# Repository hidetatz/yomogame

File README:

== Emulators & licensing

NES — src/nes/ is copied and modified from Esp32-S3-nes-emulator-by-DSN (https://github.com/derdacavga/Esp32-S3-nes-emulator-by-DSN) imported at commit 030c4b8.
Some modifications are made.

Game Boy — src/gb/ is copied and modified from Peanut-GB (https://github.com/deltabeard/Peanut-GB) .
Some modifications are made.

== License

The upstream NES emulator code is licensed under the GNU General Public
License v3 (see the LICENSE file, copied from the DSN repository; the
Nofrendo core originates as GPL‑licensed code by Matthew Conte). src/nes/ in
this repository is a derivative work and remains under the GPL.

Peanut-GB and minigb_apu (src/gb/) are under the MIT License (see
src/gb/peanut_gb.h and src/gb/LICENSE.minigb_apu); their notices are retained.
MIT imposes no copyleft, but this code is combined into the same binary as the
GPL NES core, so the paragraph below applies to the whole firmware regardless.

Because the yomogame firmware links this GPL code into a single program,
any distribution of a built yomogame binary (or of a device running it) is
subject to the GPL: recipients must be able to obtain the complete
corresponding source code under the same terms. For that reason this repository
as a whole is distributed under GPL‑3.0‑or‑later.

The first‑party parts of this project (lib/audio, lib/input,
lib/volume_overlay, src/tetris/, src/scene.h, src/frame_pusher.h,
src/yomogame.h, src/main.cpp, src/gb/gb_scene.h, src/gb/gb_core.c) are
written by the yomogame author. They are released here under the GPL as part of
the combined work.

== Assets

Background music and sound effects are used courtesy of:

イワシロ音楽素材
https://iwashiro-sounds.work/

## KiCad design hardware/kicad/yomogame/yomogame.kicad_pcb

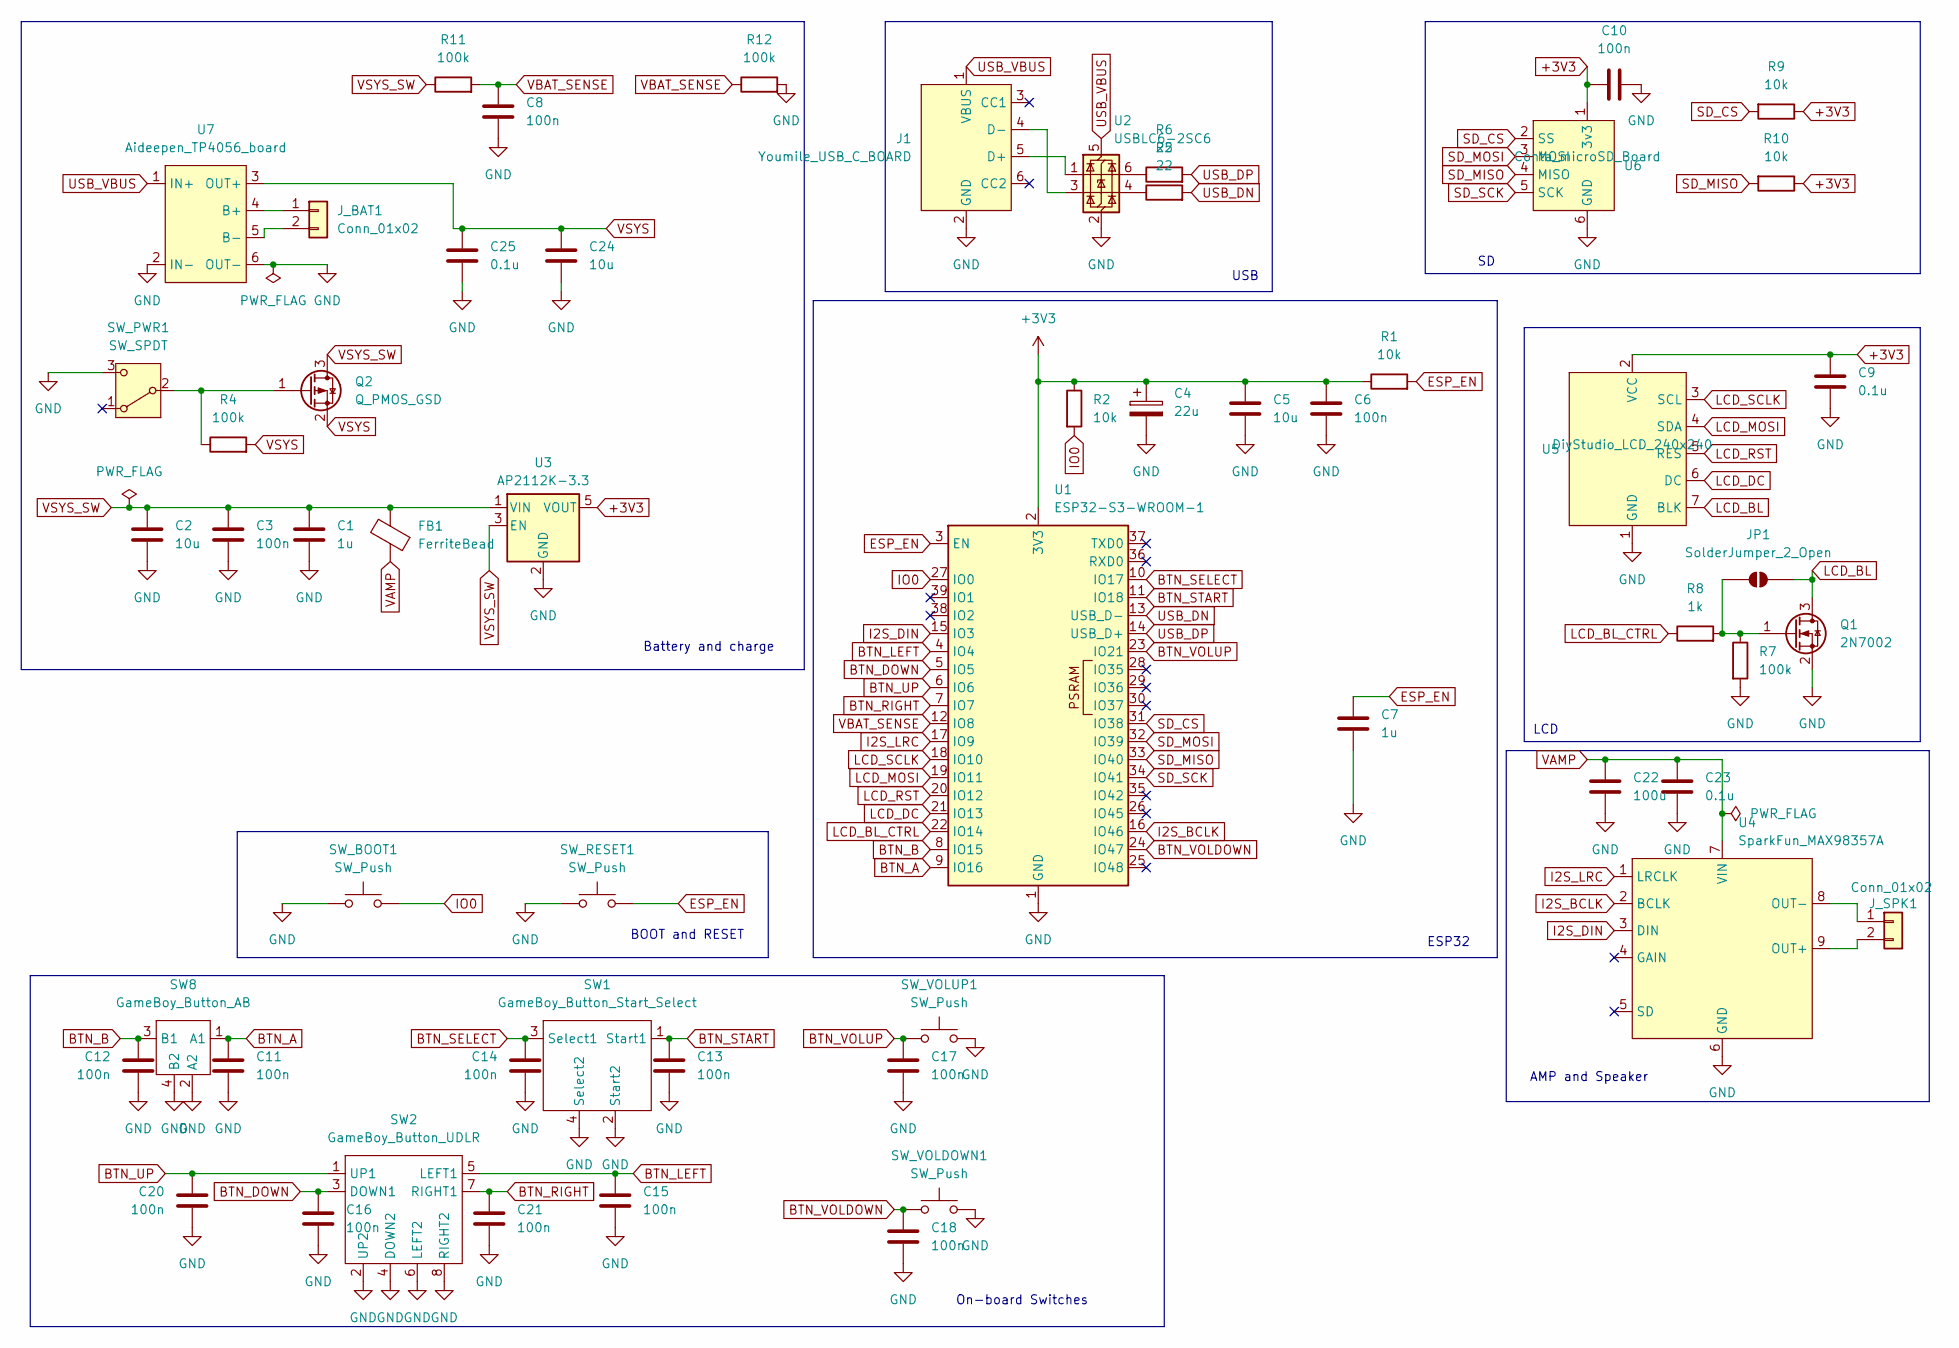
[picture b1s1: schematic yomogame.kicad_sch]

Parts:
C1, C7: 1u; C_0805_2012Metric_Pad1.18x1.45mm_HandSolder
C2, C5, C24: 10u; C_0805_2012Metric_Pad1.18x1.45mm_HandSolder
C3, C6, C8, C10, C11, C12, C13, C14, C15, C16, C17, C18, C20, C21: 100n; C_0805_2012Metric_Pad1.18x1.45mm_HandSolder
C4: 22u; C_1206_3216Metric_Pad1.33x1.80mm_HandSolder
C9, C23, C25: 0.1u; C_0805_2012Metric_Pad1.18x1.45mm_HandSolder
C22: 100u; CP_Radial_D5.0mm_P2.50mm
FB1: FerriteBead; L_0805_2012Metric_Pad1.05x1.20mm_HandSolder
J1: Youmile_USB_C_BOARD
JP1: SolderJumper_2_Open; SolderJumper-2_P1.3mm_Open_Pad1.0x1.5mm
J_BAT1: Conn_01x02; JST_PH_B2B-PH-K_1x02_P2.00mm_Vertical
J_SPK1: Conn_01x02; JST_PH_B2B-PH-K_1x02_P2.00mm_Vertical
Q1: 2N7002; SOT-23_Handsoldering
Q2: Q_PMOS_GSD; SOT-23_Handsoldering
R1, R2, R9, R10: 10k; R_0805_2012Metric_Pad1.20x1.40mm_HandSolder
R4, R7, R11, R12: 100k; R_0805_2012Metric_Pad1.20x1.40mm_HandSolder
R5, R6: 22; R_0805_2012Metric_Pad1.20x1.40mm_HandSolder
R8: 1k; R_0805_2012Metric_Pad1.20x1.40mm_HandSolder
SW1: GameBoy_Button_Start_Select; BTN_start_select
SW2: GameBoy_Button_UDLR; BTN_UDLR
SW8: GameBoy_Button_AB; BTN_AB
SW_BOOT1: SW_Push; SW_PUSH_6mm
SW_PWR1: SW_SPDT; SW_Slide_SPDT_SK-12D11VG3
SW_RESET1: SW_Push; SW_PUSH_6mm
SW_VOLDOWN1: SW_Push; SW_SMD_Side_THAU13-AB-R
SW_VOLUP1: SW_Push; SW_SMD_Side_THAU13-AB-R
U1: ESP32-S3-WROOM-1
U2: USBLC6-2SC6; SOT-23-6_Handsoldering
U3: AP2112K-3.3; SOT-23-5_HandSoldering
U4: SparkFun_MAX98357A; AMP_SparkFun_MAX98357A_I2S_AUDIO
U5: DiyStudio_LCD_240x240
U6: Conta_microSD_Board
U7: Aideepen_TP4056_board

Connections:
+3V3: C4.1, C5.1, C6.1, C9.1, C10.1, R1.1, R2.1, R9.1, R10.1, U1.2 (3V3), U3.5 (VOUT), U5.2 (VCC), U6.1 (3v3)
BTN_A: C11.1, SW8.1 (A1), U1.9 (IO16)
BTN_B: C12.1, SW8.3 (B1), U1.8 (IO15)
BTN_DOWN: C16.1, SW2.3 (DOWN1), U1.5 (IO5)
BTN_LEFT: C15.1, SW2.5 (LEFT1), U1.4 (IO4)
BTN_RIGHT: C21.1, SW2.7 (RIGHT1), U1.7 (IO7)
BTN_SELECT: C14.1, SW1.3 (Select1), U1.10 (IO17)
BTN_START: C13.1, SW1.1 (Start1), U1.11 (IO18)
BTN_UP: C20.1, SW2.1 (UP1), U1.6 (IO6)
BTN_VOLDOWN: C18.1, SW_VOLDOWN1.1, U1.24 (IO47)
BTN_VOLUP: C17.1, SW_VOLUP1.1, U1.23 (IO21)
ESP_EN: C7.1, R1.2, SW_RESET1.2, U1.3 (EN)
GND: C1.2, C2.2, C3.2, C4.2, C5.2, C6.2, C7.2, C8.2, C9.2, C10.2, C11.2, C12.2, C13.2, C14.2, C15.2, C16.2, C17.2, C18.2, C20.2, C21.2, C22.2, C23.2, C24.2, C25.2, J1.2 (GND), Q1.2 (S), R7.2, R12.2, SW1.2 (Start2), SW1.4 (Select2), SW2.2 (UP2), SW2.4 (DOWN2), SW2.6 (LEFT2), SW2.8 (RIGHT2), SW8.2 (A2), SW8.4 (B2), SW_BOOT1.1, SW_PWR1.3 (C), SW_RESET1.1, SW_VOLDOWN1.2, SW_VOLUP1.2, U1.1 (GND), U1.40 (GND), U1.41 (GND), U2.2 (GND), U3.2 (GND), U4.6 (GND), U5.1 (GND), U6.6 (GND), U7.2 (IN-), U7.6 (OUT-)
I2S_BCLK: U1.16 (IO46), U4.2 (BCLK)
I2S_DIN: U1.15 (IO3), U4.3 (DIN)
I2S_LRC: U1.17 (IO9), U4.1 (LRCLK)
IO0: R2.2, SW_BOOT1.2, U1.27 (IO0)
LCD_BL: JP1.2 (B), Q1.3 (D), U5.7 (BLK)
LCD_BL_CTRL: R8.1, U1.22 (IO14)
LCD_DC: U1.21 (IO13), U5.6 (DC)
LCD_MOSI: U1.19 (IO11), U5.4 (SDA)
LCD_RST: U1.20 (IO12), U5.5 (RES)
LCD_SCLK: U1.18 (IO10), U5.3 (SCL)
unnamed: J1.5 (D+), U2.1 (I/O1)
unnamed: J1.4 (D-), U2.3 (I/O2)
unnamed: JP1.1 (A), Q1.1 (G), R7.1, R8.2
unnamed: J_BAT1.1, U7.4 (B+)
unnamed: J_BAT1.2, U7.5 (B-)
unnamed: J_SPK1.1, U4.8 (OUT-)
unnamed: J_SPK1.2, U4.9 (OUT+)
unnamed: Q2.1 (G), R4.1, SW_PWR1.2 (B)
unnamed: R5.1, U2.4 (I/O2)
unnamed: R6.1, U2.6 (I/O1)
SD_CS: R9.2, U1.31 (IO38), U6.2 (SS)
SD_MISO: R10.2, U1.33 (IO40), U6.4 (MISO)
SD_MOSI: U1.32 (IO39), U6.3 (MOSI)
SD_SCK: U1.34 (IO41), U6.5 (SCK)
USB_DN: R5.2, U1.13 (USB_D-)
USB_DP: R6.2, U1.14 (USB_D+)
USB_VBUS: J1.1 (VBUS), U2.5 (VBUS), U7.1 (IN+)
VAMP: C22.1, C23.1, FB1.1, U4.7 (VIN)
VBAT_SENSE: C8.1, R11.2, R12.1, U1.12 (IO8)
VSYS: C24.1, C25.1, Q2.2 (S), R4.2, U7.3 (OUT+)
VSYS_SW: C1.1, C2.1, C3.1, FB1.2, Q2.3 (D), R11.1, U3.1 (VIN), U3.3 (EN)

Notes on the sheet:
On-board Switches
ESP32
BOOT and RESET
AMP and Speaker
Battery and charge
LCD
USB

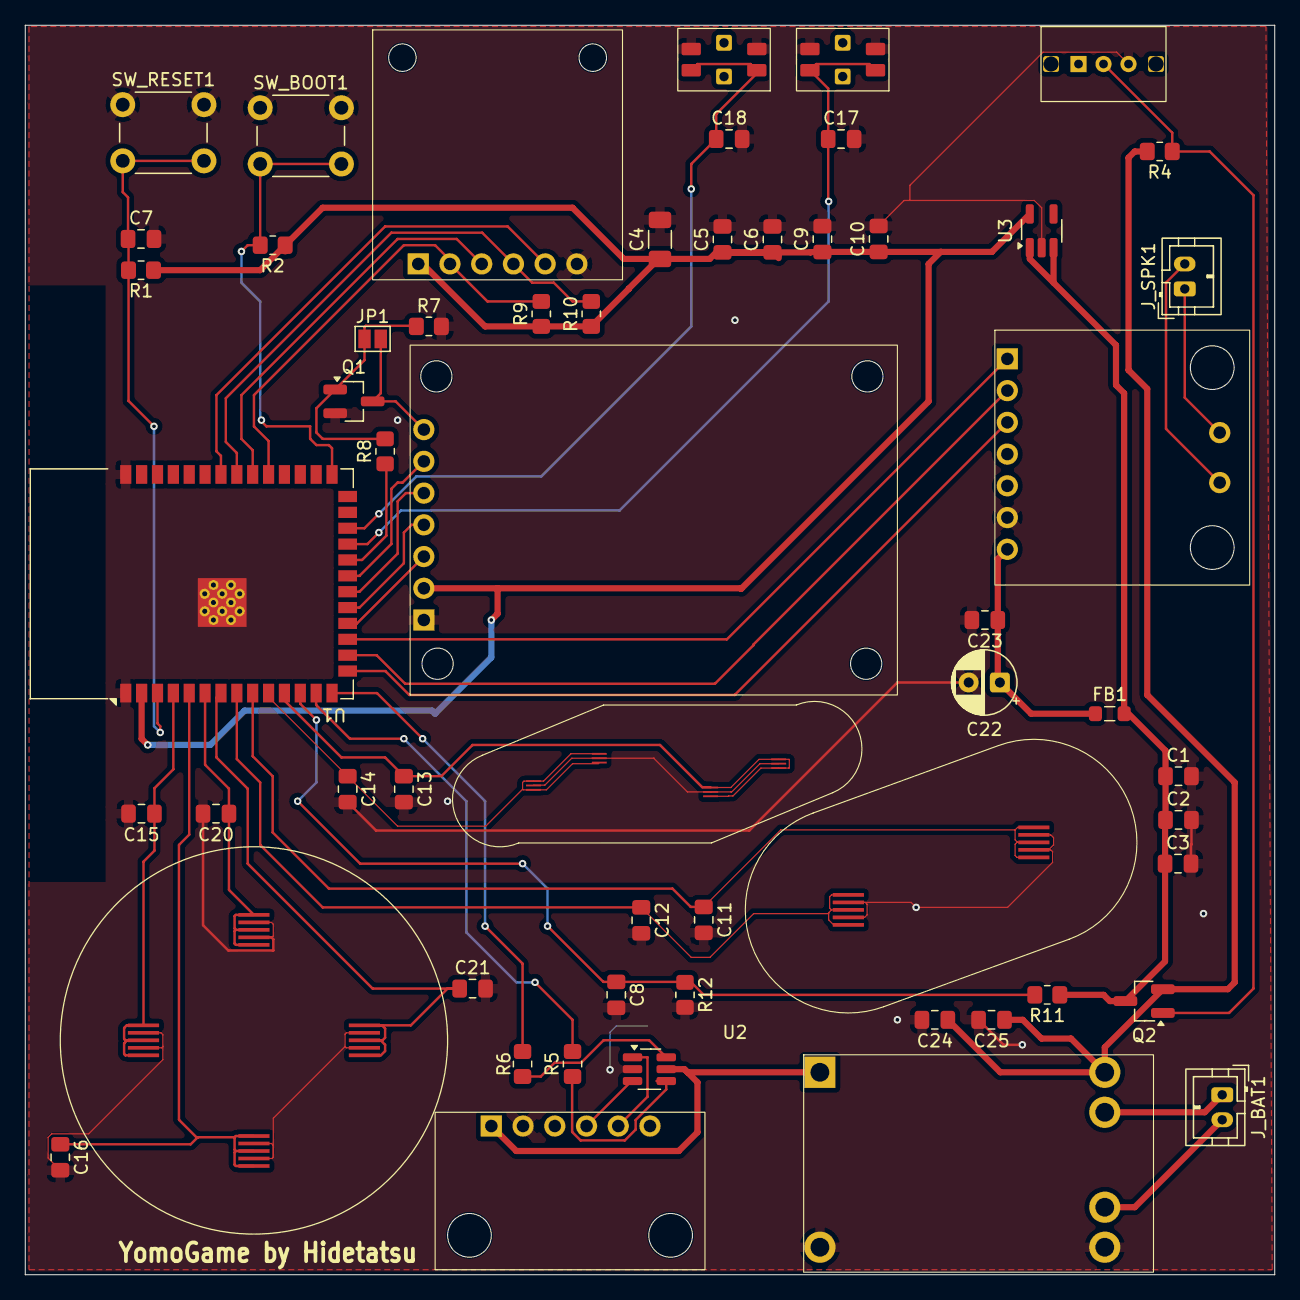
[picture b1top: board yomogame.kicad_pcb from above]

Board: 2 copper layers, 100.0 x 100.0 mm, 57 parts (0 on the bottom side), 44 nets.

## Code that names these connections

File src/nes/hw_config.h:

#pragma once

#include <SPI.h>

// The DSN emulator's compile-time sound path (built-in i2s_driver_install) is
// disabled: audio is bridged into audio::Audio via nes_audio_push() instead.
#define ENABLE_SOUND 0

// SD card has its own dedicated SPI bus on this board, separate from the LCD
// (TFT_eSPI owns the other hardware SPI peripheral via TFT_SCLK/TFT_MOSI).
#define SD_CS   38
#define SD_MISO 40
#define SD_SCK  41
#define SD_MOSI 39

// Lazily-initialised SPI bus for the SD card. Shared by nes_scene.h and
// gb_scene.h (whichever scene runs first performs the one-time begin()).
inline SPIClass& sd_spi_bus() {
  static SPIClass bus(HSPI);
  static bool started = false;
  if (!started) {
    bus.begin(SD_SCK, SD_MISO, SD_MOSI, SD_CS);
    started = true;
  }
  return bus;
}
